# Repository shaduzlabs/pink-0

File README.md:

# pink-0

This repository contains the source code and the schematics for an Ableton Link to clock/reset converter.

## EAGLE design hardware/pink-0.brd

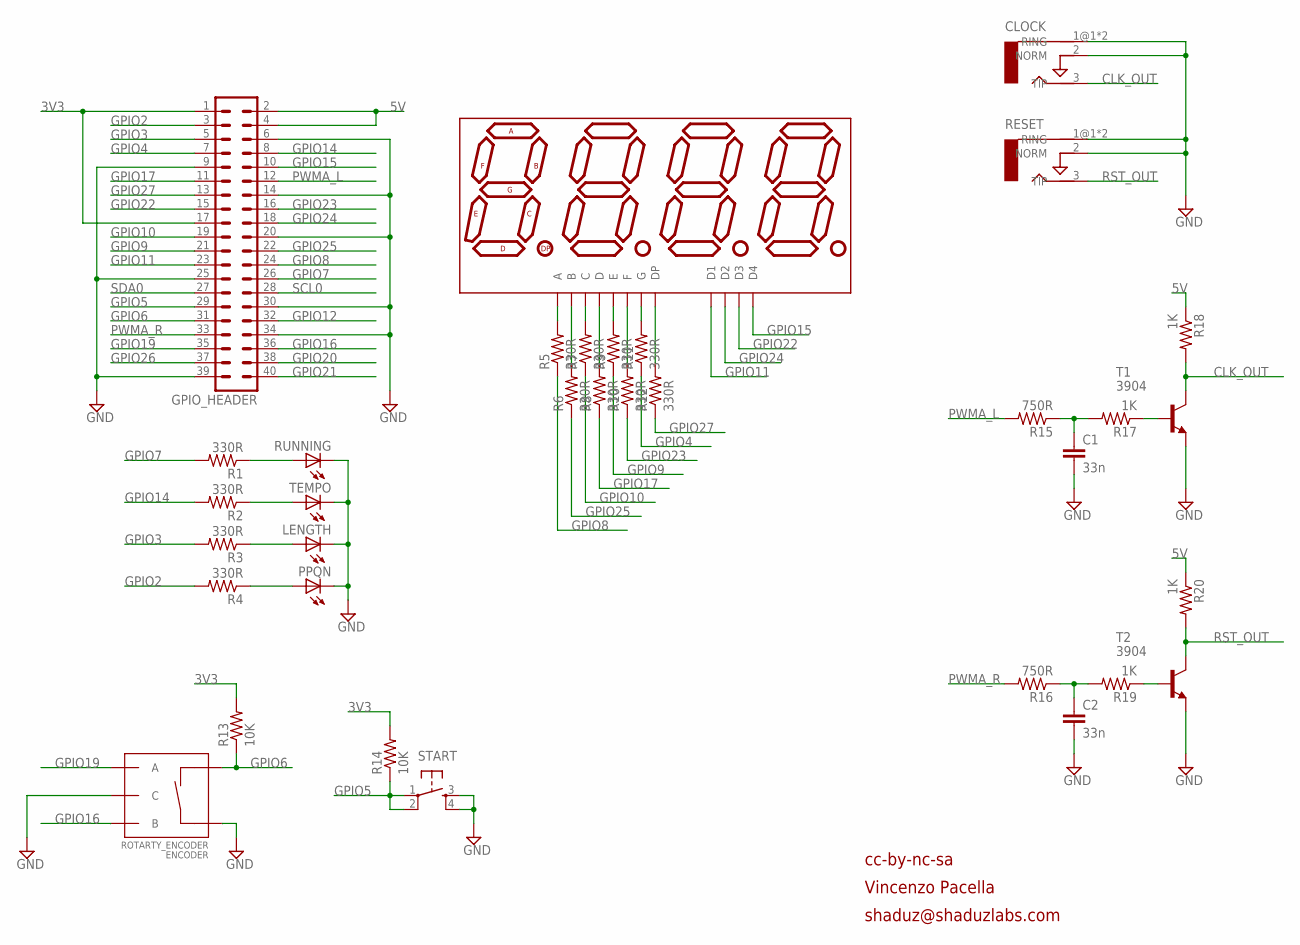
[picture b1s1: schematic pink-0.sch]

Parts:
C1, C2: 33n; 0603-CAP
CLOCK: AUDIO-JACKERTHENVAR; ERTHENVAR-JACK
DISP1: QDSP6064; DIL12
ENCODER: ROTARTY_ENCODER; ROTARY_ENC_PLAIN
GPIO_HEADER: PIZERO_THROUGH_HOLE; PIZERO_THOUGH_HOLE
LENGTH: LED0603; LED-0603
PPQN: LED0603; LED-0603
R1, R2, R3, R4, R5, R6, R7, R8, R9, R10, R11, R12: 330R; R0402
R13, R14: 10K; R0402
R15, R16: 750R; R0402
R17, R18, R19, R20: 1K; R0402
RESET: AUDIO-JACKERTHENVAR; ERTHENVAR-JACK
RUNNING: LED0603; LED-0603
START: TAC_SWITCHPTH; TACTILE-PTH
T1, T2: 3904; SOT23-BEC
TEMPO: LED0603; LED-0603

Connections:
3V3: GPIO_HEADER.1, GPIO_HEADER.17, R13.2, R14.2
5V: GPIO_HEADER.2, GPIO_HEADER.4, R18.1, R20.1
CLK_OUT: CLOCK.3 (TIP), R18.2, T1.C
GND: C1.2, C2.2, CLOCK.1@1 (RING), CLOCK.1@2 (RING), CLOCK.2 (NORM), ENCODER.C, ENCODER.SW+, GPIO_HEADER.6, GPIO_HEADER.9, GPIO_HEADER.14, GPIO_HEADER.20, GPIO_HEADER.25, GPIO_HEADER.30, GPIO_HEADER.34, GPIO_HEADER.39, LENGTH.C, PPQN.C, RESET.1@1 (RING), RESET.1@2 (RING), RESET.2 (NORM), RUNNING.C, START.3, START.4, T1.E, T2.E, TEMPO.C
GPIO2: GPIO_HEADER.3, R4.2
GPIO3: GPIO_HEADER.5, R3.2
GPIO4: GPIO_HEADER.7, R11.1
GPIO5: GPIO_HEADER.29, R14.1, START.1, START.2
GPIO6: ENCODER.SW-, GPIO_HEADER.31, R13.1
GPIO7: GPIO_HEADER.26, R1.2
GPIO8: GPIO_HEADER.24, R5.1
GPIO9: GPIO_HEADER.21, R9.1
GPIO10: GPIO_HEADER.19, R7.1
GPIO11: DISP1.1 (D1), GPIO_HEADER.23
GPIO12: GPIO_HEADER.32
GPIO14: GPIO_HEADER.8, R2.2
GPIO15: DISP1.6 (D4), GPIO_HEADER.10
GPIO16: ENCODER.B, GPIO_HEADER.36
GPIO17: GPIO_HEADER.11, R8.1
GPIO19: ENCODER.A, GPIO_HEADER.35
GPIO20: GPIO_HEADER.38
GPIO21: GPIO_HEADER.40
GPIO22: DISP1.4 (D3), GPIO_HEADER.15
GPIO23: GPIO_HEADER.16, R10.1
GPIO24: DISP1.10 (D2), GPIO_HEADER.18
GPIO25: GPIO_HEADER.22, R6.1
GPIO26: GPIO_HEADER.37
GPIO27: GPIO_HEADER.13, R12.1
unnamed: DISP1.12 (A), R5.2
unnamed: DISP1.11 (B), R6.2
unnamed: DISP1.3 (C), R7.2
unnamed: DISP1.8 (D), R8.2
unnamed: R1.1, RUNNING.A
unnamed: R2.1, TEMPO.A
unnamed: DISP1.2 (E), R9.2
unnamed: DISP1.9 (F), R10.2
unnamed: DISP1.7 (G), R11.2
unnamed: DISP1.5 (DP), R12.2
unnamed: R19.1, T2.B
unnamed: R17.1, T1.B
unnamed: C1.1, R15.1, R17.2
unnamed: LENGTH.A, R3.1
unnamed: PPQN.A, R4.1
unnamed: C2.1, R16.1, R19.2
PWMA_L: GPIO_HEADER.12, R15.2
PWMA_R: GPIO_HEADER.33, R16.2
RST_OUT: R20.2, RESET.3 (TIP), T2.C
SCL0: GPIO_HEADER.28
SDA0: GPIO_HEADER.27

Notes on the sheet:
cc-by-nc-sa
Vincenzo Pacella
shaduz@shaduzlabs.com

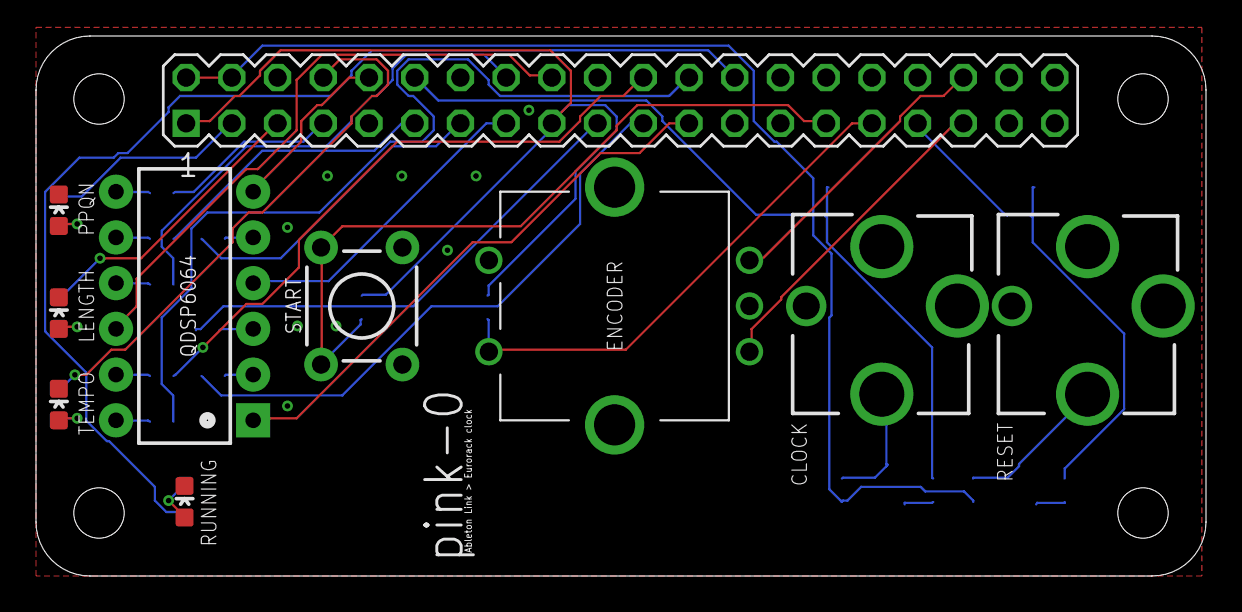
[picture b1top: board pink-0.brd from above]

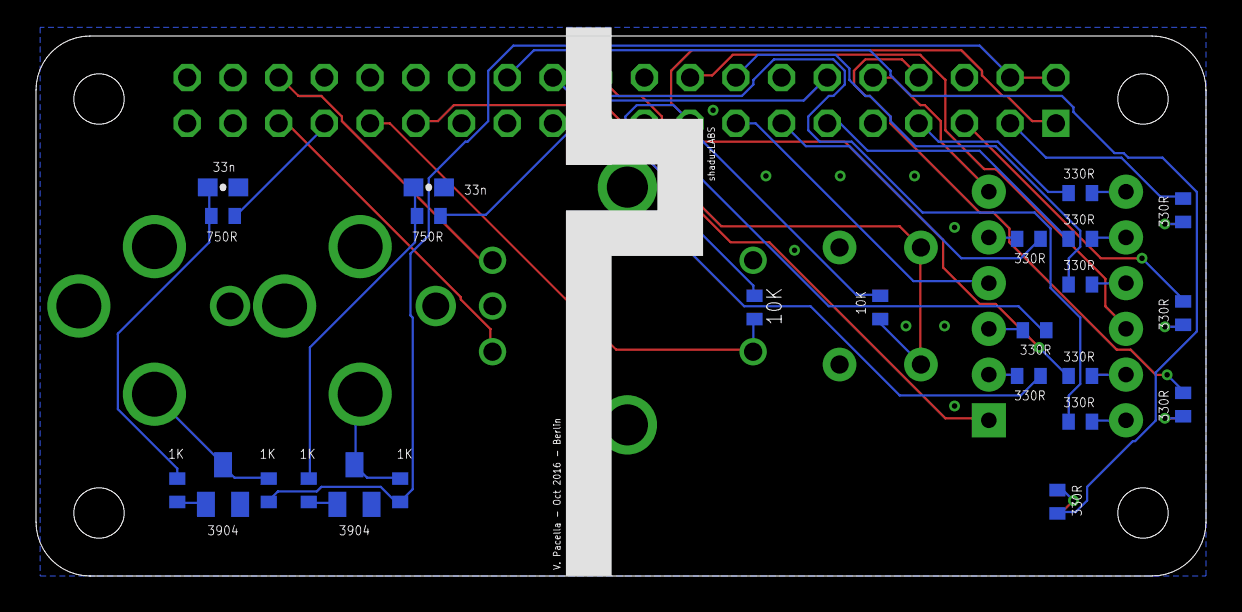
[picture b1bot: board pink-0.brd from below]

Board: 2 copper layers, 65.0 x 30.0 mm, 34 parts (24 on the bottom side), 43 nets.

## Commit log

2017-02-14 fix install script
2017-02-14 update stylesheet and js
2017-02-14 minor changes
2017-02-21 first import from private repo
2017-02-24 add UserInterfaceNone
2017-02-24 update install script
2017-02-24 formatting
2017-03-07 add pink-0 BOM
2017-03-08 play immediately when no ui is available
2017-03-08 fix automatic start of the daemon
2017-03-11 add cereal and nmws submodules
2017-03-11 add clang-format configuration
2017-03-11 add UserInterfaceWebSocket [wip], cleanup
2017-03-12 UserInterfaceWebSocket implementation, Pink interface update
2017-03-12 add javascript client
2017-03-12 bump version: 0.1.0
2017-03-13 update web ui
2017-03-13 update install script, fix websocket binding
2017-03-13 web ui: update sliders
2017-03-13 minor fixes
2017-03-14 set loop length step to 0.25
2017-03-14 update nmws version
2017-03-18 #3 - add missing hashbang in install script
2017-03-19 use latest version of Ableton Link
2017-03-19 add RtAudio submodule
2017-03-19 first RtAudio implementation
2017-03-19 update Audio buffer config
2017-03-19 update rtaudio link config, disable daemon mode from cli
2017-03-19 add missing include path
2017-03-19 fix main CMakeLists
2017-03-19 change sampling rate
2017-03-20 add empty UI class for CHIP Pro
2017-03-20 CHIP Pro: first GPIO implementation
2017-03-20 fix compiler errors
2017-03-20 CHIP Pro: GPIO bugfix
2017-03-27 improve logging, minor changes
2017-03-27 update CMake configuration
2017-03-27 update nmws submodule commit
2017-04-06 add missing library to install script
2017-04-06 bump version to 0.1.1
2017-04-06 fix default audio buffer value
2017-04-06 reset upon start
2018-05-24 Backlink to CADLAB.io has been added.
2018-07-08 use updated link version
2018-07-08 use updated nmws version
2018-07-08 Backlink to CADLAB.io has been added. (reverted from commit d6a488abdb5d1f8d3aa95865420083ca13b9ef9a)
2018-09-12 Adapt to latest changes in Link API

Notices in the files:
parts and their libraries:
SparkFun-Displays: Licensing: Creative Commons ShareAlike 4.0 International - https://creativecommons.org/licenses/by-sa/4.0
